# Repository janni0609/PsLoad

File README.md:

# PsLoad
 Power Supply and DC Load

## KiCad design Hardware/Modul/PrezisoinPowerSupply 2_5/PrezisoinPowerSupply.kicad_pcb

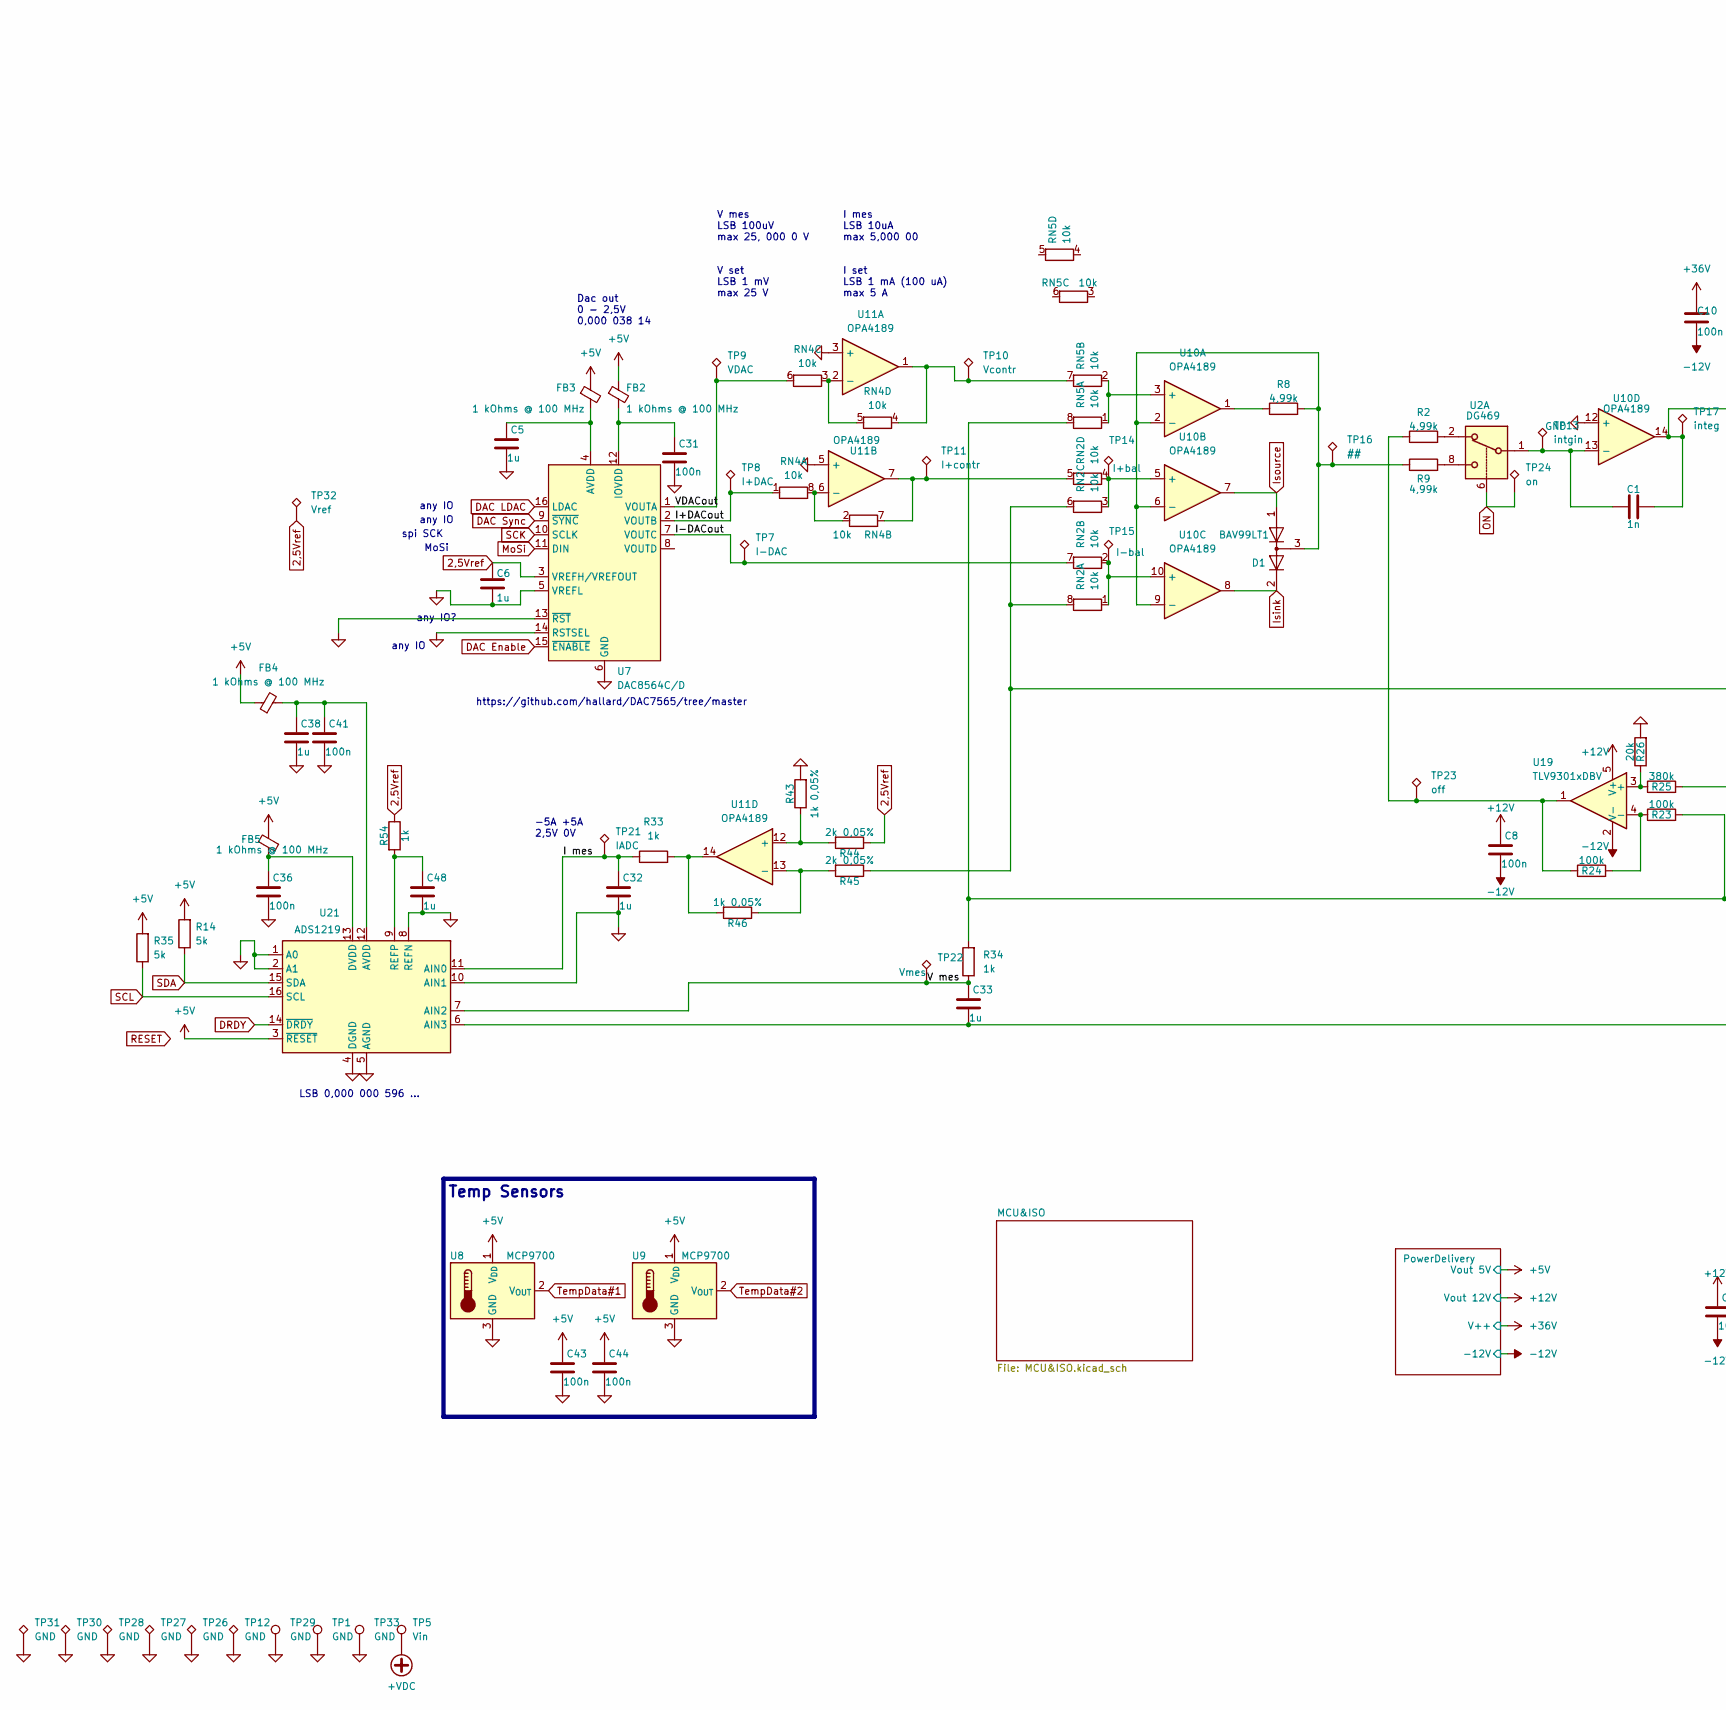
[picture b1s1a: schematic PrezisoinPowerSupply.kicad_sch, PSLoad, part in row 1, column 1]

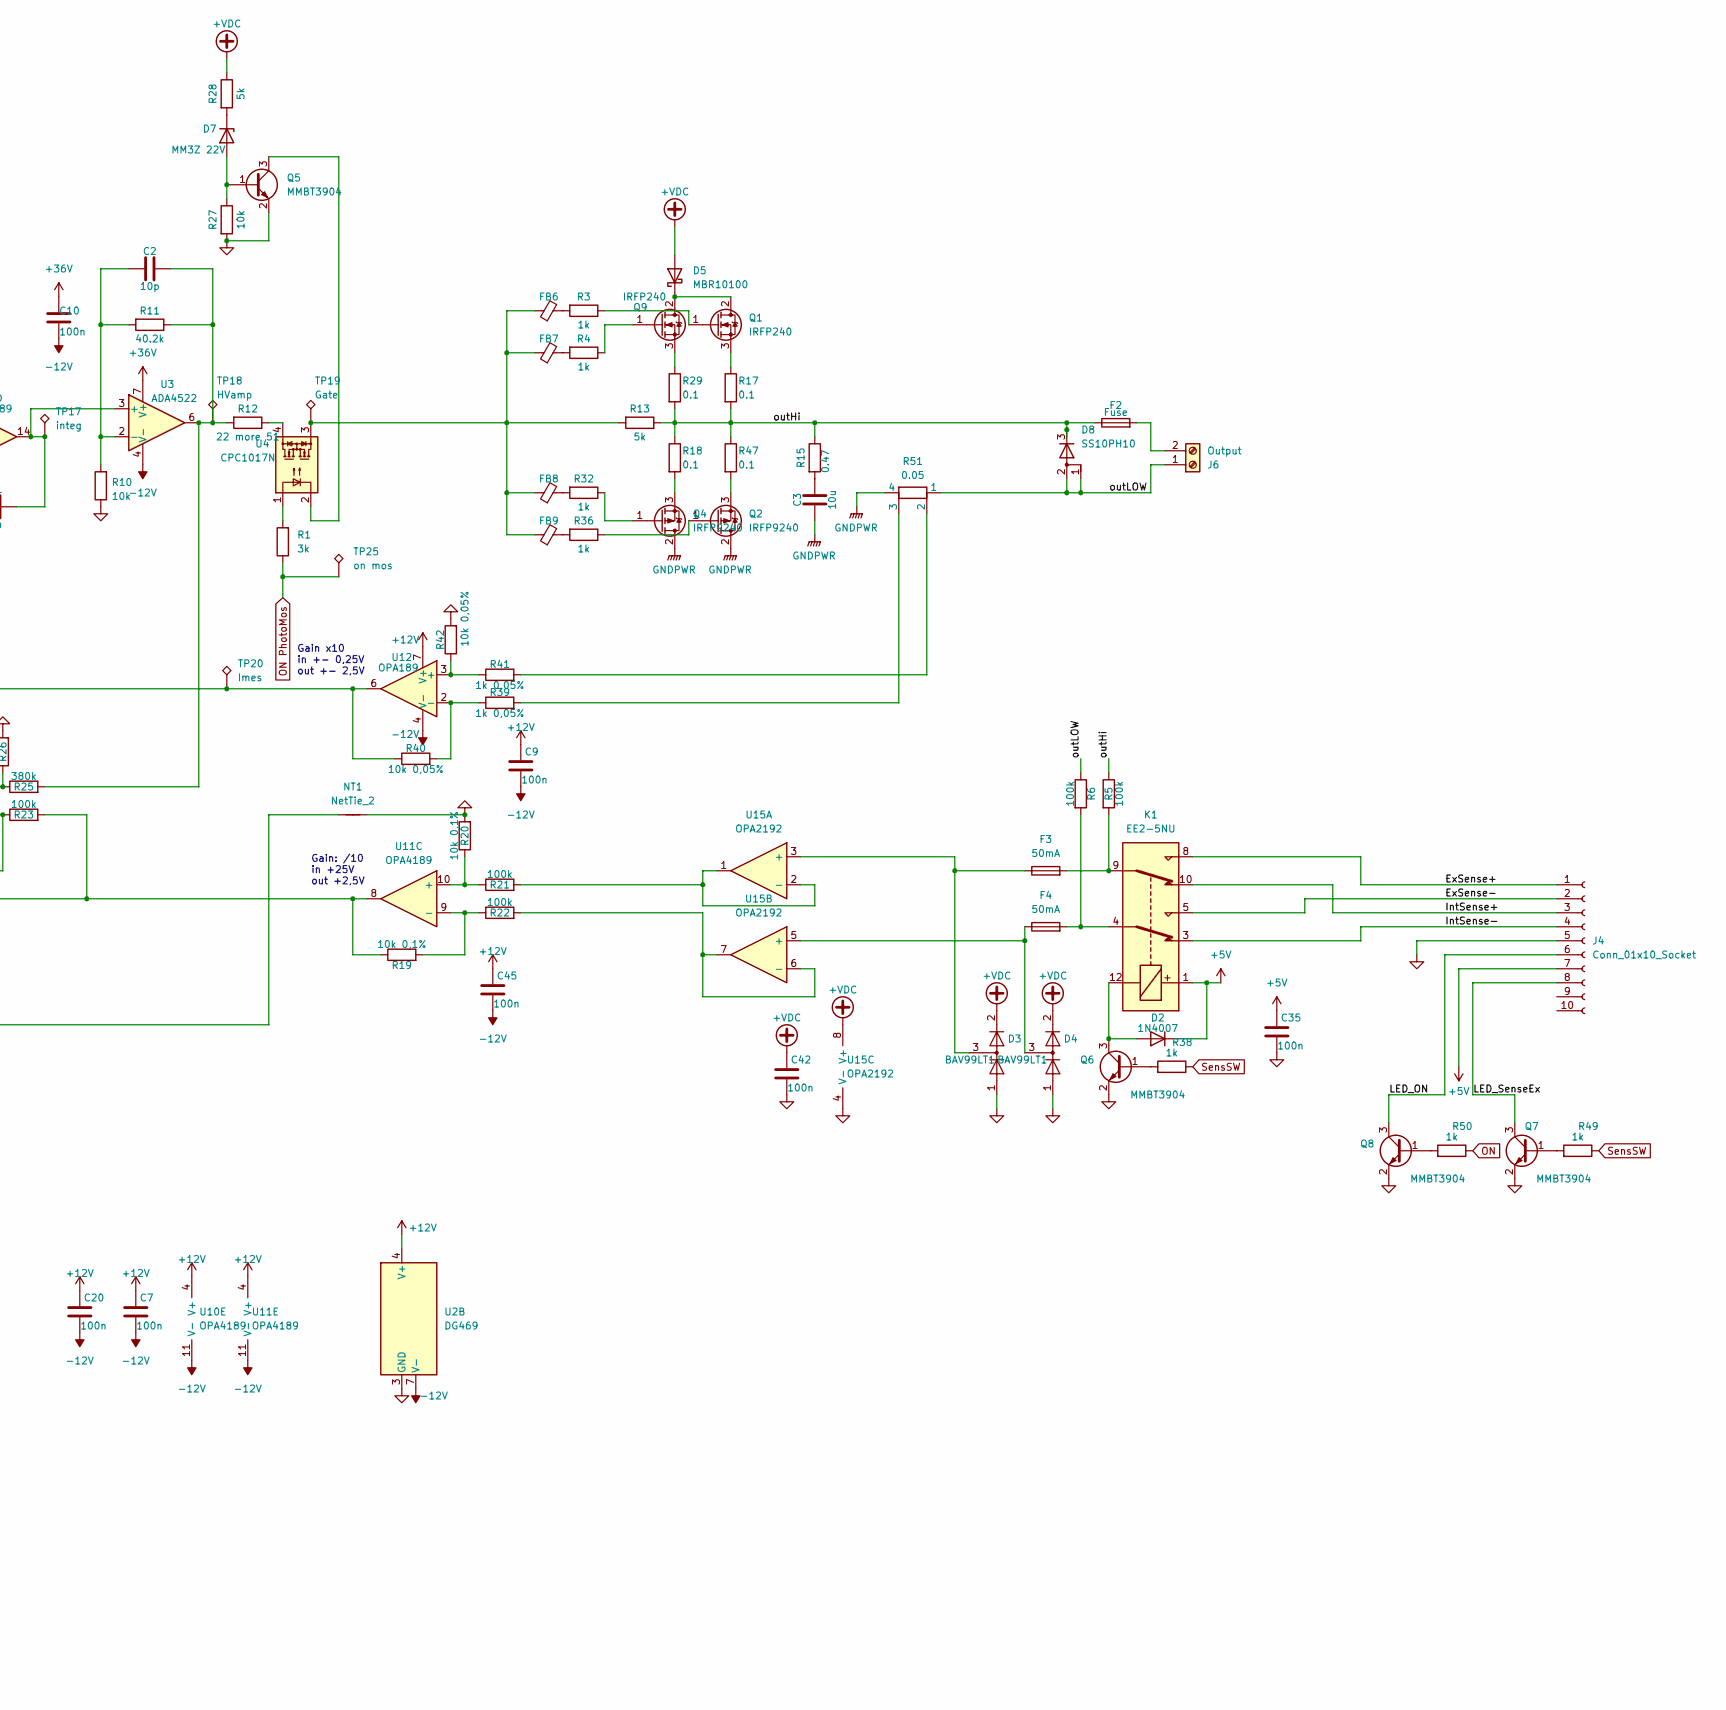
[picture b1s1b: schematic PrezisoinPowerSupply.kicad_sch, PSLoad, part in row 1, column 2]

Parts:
C1: 1n; C_0603_1608Metric
C2: 10p; C_0603_1608Metric
C3: 10u; C_1206_3216Metric
C5, C6, C32, C33, C38, C48: 1u; C_0603_1608Metric
C7, C8, C9, C10, C20, C31, C35, C36, C41, C42, C43, C44, C45: 100n; C_0603_1608Metric
D1: BAV99LT1; SOT-23
D2: 1N4007; D_SOD-123F
D3, D4: BAV99LT1; SOT-23-3
D5: MBR10100; TO-220-2_Vertical
D7: MM3Z 22V; D_SOD-323F
D8: SS10PH10; TO-277A
F2: Fuse; Fuse_Littelfuse-NANO2-451_453
F3, F4: 50mA; Fuse_0402_1005Metric
FB2, FB3, FB4, FB5, FB6, FB7, FB8, FB9: 1 kOhms @ 100 MHz; L_0603_1608Metric
J4: Conn_01x10_Socket; JST_GH_BM10B-GHS-TBT_1x10-1MP_P1.25mm_Vertical
J6: Output; AMASS_XT30PW-F_1x02_P2.50mm_Horizontal
K1: EE2-5NU; Relay_DPDT_Kemet_EE2_NU
NT1: NetTie_2; NetTie-2_SMD_Pad0.5mm
Q1, Q9: IRFP240; TO-247-3_Vertical
Q2, Q4: IRFP9240; TO-247-3_Vertical
Q5, Q6, Q7, Q8: MMBT3904; SOT-23-3
R1: 3k; R_0603_1608Metric
R2, R8, R9: 4,99k; R_0603_1608Metric
R3, R4, R32, R33, R34, R36, R38, R49, R50, R54: 1k; R_0603_1608Metric
R5, R6, R21, R22, R23, R24: 100k; R_0603_1608Metric
R10, R27: 10k; R_0603_1608Metric
R11: 40.2k; R_0603_1608Metric
R12: 22 more 51; R_0603_1608Metric
R13, R14, R28, R35: 5k; R_0603_1608Metric
R15: 0.47; R_1206_3216Metric
R17, R18, R29, R47: 0.1; R_Bare_Metal_Element_L16.3mm_W4.8mm_P15.30mm
R19, R20: 10k 0,1%; R_0603_1608Metric
R25: 380k; R_0603_1608Metric
R26: 20k; R_0603_1608Metric
R39, R41, R43, R46: 1k 0,05%; R_0603_1608Metric
R40, R42: 10k 0,05%; R_0603_1608Metric
R44, R45: 2k 0,05%; R_0603_1608Metric
R51: 0.05; R 2728 4Wire
RN2, RN4, RN5: 10k; R_Array_Convex_4x0612
TP1, TP29, TP33: GND; SMD Test Point PCWCTE
TP5: Vin; SMD Test Point PCWCTE
TP7: I-DAC; TestPoint_Pad_D1.5mm
TP8: I+DAC; TestPoint_Pad_D1.5mm
TP9: VDAC; TestPoint_Pad_D1.5mm
TP10: Vcontr; TestPoint_Pad_D1.5mm
TP11: I+contr; TestPoint_Pad_D1.5mm
TP12, TP26, TP27, TP28, TP30, TP31: GND; TestPoint_Pad_D1.5mm
TP13: intgin; TestPoint_Pad_D1.5mm
TP14: I+bal; TestPoint_Pad_D1.5mm
TP15: I-bal; TestPoint_Pad_D1.5mm
TP16: ##; TestPoint_Pad_D1.5mm
TP17: integ; TestPoint_Pad_D1.5mm
TP18: HVamp; TestPoint_Pad_D1.5mm
TP19: Gate; TestPoint_Pad_D1.5mm
TP20: Imes; TestPoint_Pad_D1.5mm
TP21: IADC; TestPoint_Pad_D1.5mm
TP22: Vmes; TestPoint_Pad_D1.5mm
TP23: off; TestPoint_Pad_D1.5mm
TP24: on; TestPoint_Pad_D1.5mm
TP25: on mos; TestPoint_Pad_D1.5mm
TP32: Vref; TestPoint_Pad_D1.5mm
U2: DG469; SOIC-8_3.9x4.9mm_P1.27mm
U3: ADA4522; SOIC-8_3.9x4.9mm_P1.27mm
U4: CPC1017N; SOP-4_3.8x4.1mm_P2.54mm
U7: DAC8564C/D; TSSOP-16_4.4x5mm_P0.65mm
U8, U9: MCP9700; TO-92_Inline
U10, U11: OPA4189; SOIC-14_3.9x8.7mm_P1.27mm
U12: OPA189; SOIC-8_3.9x4.9mm_P1.27mm
U15: OPA2192; SOIC-8_3.9x4.9mm_P1.27mm
U19: TLV9301xDBV; SOT-23-5
U21: ADS1219; TSSOP-16_4.4x5mm_P0.65mm

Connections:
2,5Vref: C6.1, R44.1, R54.1, TP32.1, U7.3 (VREFH/VREFOUT)
+5V: C35.1, C43.1, C44.1, D2.1 (K), FB2.1, FB3.1, FB4.1, FB5.2, J4.7, K1.1, R14.2, R35.2, U8.1 (V_{DD}), U9.1 (V_{DD}), U21.3 (~RESET); also elsewhere on the board
+12V: C7.1, C8.1, C9.1, C20.1, C45.1, U2.4 (V+), U10.4 (V+), U11.4 (V+), U12.7 (V+), U19.5 (V+); also elsewhere on the board
+36V: C10.1, U3.7 (V+); also elsewhere on the board
-12V: C7.2, C8.2, C9.2, C10.2, C20.2, C45.2, U2.7 (V-), U3.4 (V-), U10.11 (V-), U11.11 (V-), U12.4 (V-), U19.2 (V-); also elsewhere on the board
/ExSense+: J4.1, K1.8
/ExSense-: J4.2, K1.5
/I mes: C32.1, R33.1, TP21.1, U21.11 (AIN0)
/I+DACout: RN4.1 (R1.1), TP8.1, U7.2 (VOUTB)
/I-DACout: RN2.7 (R2.2), TP7.1, U7.7 (VOUTC)
/IntSense+: J4.3, K1.10
/IntSense-: J4.4, K1.3
/LED_ON: J4.6, Q8.3 (C)
/LED_SenseEx: J4.8, Q7.3 (C)
/V mes: C33.1, R34.1, TP22.1, U21.7 (AIN2)
/VDACout: RN4.6 (R3.2), TP9.1, U7.1 (VOUTA)
/outHi: D8.3 (K), F2.1, R5.1, R13.1, R15.1, R17.2, R18.1, R29.2, R47.1
/outLOW: D8.1 (A), D8.2 (A), J6.1, R6.1, R51.1
DAC Enable: U7.15 (~ENABLE); also elsewhere on the board
DAC LDAC: U7.16 (LDAC); also elsewhere on the board
DAC Sync: U7.9 (~SYNC); also elsewhere on the board
DRDY: U21.14 (~DRDY); also elsewhere on the board
GND: C5.2, C6.2, C31.2, C32.2, C35.2, C36.2, C38.2, C41.2, C42.2, C43.2, C44.2, C48.2, D3.1 (K), D4.1 (K), J4.5, NT1.2, Q5.2 (E), Q6.2 (E), Q7.2 (E), Q8.2 (E), R10.1, R20.2, R26.2, R27.2, R42.2, R43.2, TP1.1, TP12.1, TP26.1, TP27.1, TP28.1, TP29.1, TP30.1, TP31.1, TP33.1, U2.3 (GND), U7.5 (VREFL), U7.6 (GND), U7.13 (~RST), U7.14 (RSTSEL), U8.3 (GND), U9.3 (GND), U10.12 (+), U11.3 (+), U11.5 (+), U15.4 (V-), U21.1 (A0), U21.2 (A1), U21.4 (DGND), U21.5 (AGND), U21.8 (REFN), U21.10 (AIN1); also elsewhere on the board
GNDPWR: C3.1, Q2.2 (D), Q4.2 (D), R51.4; also elsewhere on the board
Isink: D1.2 (A), U10.8
Isource: D1.1 (K), U10.7
MoSi: U7.11 (DIN); also elsewhere on the board
unnamed: C2.2, R11.1, R12.2, R25.2, TP18.1, U3.6
unnamed: C3.2, R15.2
unnamed: D2.2 (A), K1.12, Q6.3 (C)
unnamed: D5.1 (K), Q1.2 (D), Q9.2 (D)
unnamed: D7.2 (A), Q5.1 (B), R27.1
unnamed: D7.1 (K), R28.2
unnamed: F3.2, K1.9, R5.2
unnamed: F4.2, K1.4, R6.2
unnamed: FB6.1, FB7.1, FB8.1, FB9.1, R13.2, TP19.1, U4.3
unnamed: FB6.2, R3.2
unnamed: FB7.2, R4.2
unnamed: FB8.2, R32.2
unnamed: FB9.2, R36.2
unnamed: F2.2, J6.2
unnamed: Q1.1 (G), R3.1
unnamed: Q1.3 (S), R17.1
unnamed: Q2.1 (G), R36.1
unnamed: Q2.3 (S), R47.2
unnamed: Q4.1 (G), R32.1
unnamed: Q4.3 (S), R18.2
unnamed: Q5.3 (C), U4.2
unnamed: Q6.1 (B), R38.2
unnamed: Q7.1 (B), R49.2
unnamed: Q8.1 (B), R50.2
unnamed: Q9.1 (G), R4.1
unnamed: Q9.3 (S), R29.1
unnamed: R1.2, U4.1
unnamed: R2.1, R24.1, TP23.1, U19.1
unnamed: R2.2, U2.2
unnamed: R8.1, U10.1
unnamed: R9.2, U2.8
unnamed: R12.1, U4.4
unnamed: R33.2, R46.2, U11.14
unnamed: R39.2, R51.3
unnamed: R41.2, R51.2
unnamed: RN2.1 (R1.1), RN2.2 (R2.1), TP15.1, U10.10 (+)
unnamed: R40.1, R45.1, RN2.6 (R3.2), RN2.8 (R1.2), TP20.1, U12.6
unnamed: RN2.3 (R3.1), RN2.4 (R4.1), TP14.1, U10.5 (+)
unnamed: RN2.5 (R4.2), RN4.7 (R2.2), TP11.1, U11.7
unnamed: RN4.2 (R2.1), RN4.8 (R1.2), U11.6 (-)
unnamed: RN4.3 (R3.1), RN4.5 (R4.2), U11.2 (-)
unnamed: RN4.4 (R4.1), RN5.7 (R2.2), TP10.1, U11.1
unnamed: RN5.1 (R1.1), RN5.2 (R2.1), U10.3 (+)
unnamed: R19.1, R23.2, R34.2, RN5.8 (R1.2), U11.8
unnamed: C1.2, TP17.1, U3.3 (+), U10.14
unnamed: C2.1, R10.2, R11.2, U3.2 (-)
unnamed: C5.1, FB3.2, U7.4 (AVDD)
unnamed: C31.1, FB2.2, U7.12 (IOVDD)
unnamed: D1.3 (K), R8.2, R9.1, TP16.1, U10.2 (-), U10.6 (-), U10.9 (-)
unnamed: C1.1, TP13.1, U2.1, U10.13 (-)
unnamed: R20.1, R21.1, U11.10 (+)
unnamed: R19.2, R22.1, U11.9 (-)
unnamed: R43.1, R44.2, U11.12 (+)
unnamed: R45.2, R46.1, U11.13 (-)
unnamed: R41.1, R42.1, U12.3 (+)
unnamed: R39.1, R40.2, U12.2 (-)
unnamed: D3.3 (K), F3.1, U15.3 (+)
unnamed: R21.2, U15.1, U15.2 (-)
unnamed: D4.3 (K), F4.1, U15.5 (+)
unnamed: R22.2, U15.6 (-), U15.7
unnamed: R25.1, R26.1, U19.3 (+)
unnamed: R23.1, R24.2, U19.4 (-)
unnamed: C33.2, NT1.1, U21.6 (AIN3)
unnamed: C38.1, C41.1, FB4.2, U21.12 (AVDD)
unnamed: C36.1, FB5.1, U21.13 (DVDD)
unnamed: C48.1, R54.2, U21.9 (REFP)
ON: R50.1, TP24.1, U2.6; also elsewhere on the board
ON PhotoMos: R1.1, TP25.1; also elsewhere on the board
SCK: U7.10 (SCLK); also elsewhere on the board
SCL: R35.1, U21.16 (SCL); also elsewhere on the board
SDA: R14.1, U21.15 (SDA); also elsewhere on the board
SensSW: R38.1, R49.1; also elsewhere on the board
TempData#1: U8.2 (V_{OUT}); also elsewhere on the board
TempData#2: U9.2 (V_{OUT}); also elsewhere on the board

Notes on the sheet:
https://github.com/hallard/DAC7565/tree/master
any IO
Temp Sensors
Dac out 0 - 2,5V 0,000 038 14
LSB 0,000 000 596 ...
spi SCK
any IO?
Gain: /10 in +25V out +2,5V
MoSi
-5A +5A 2,5V 0V
V mes LSB 100uV max 25, 000 0 V
V set LSB 1 mV max 25 V
Gain x10 in +- 0,25V out +- 2,5V
I mes LSB 10uA max 5,000 00
I set LSB 1 mA (100 uA) max 5 A

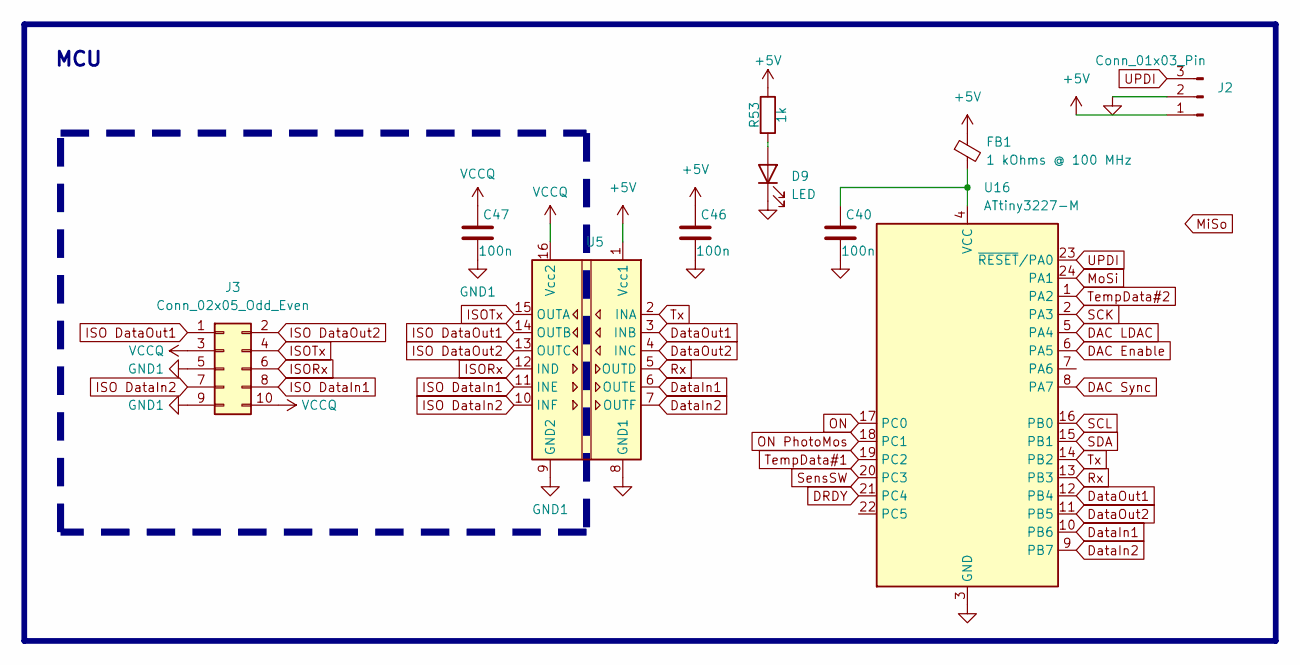
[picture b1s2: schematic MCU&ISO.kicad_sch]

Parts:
C40, C46, C47: 100n; C_0603_1608Metric
D9: LED; LED_0603_1608Metric
FB1: 1 kOhms @ 100 MHz; L_0603_1608Metric
J2: Conn_01x03_Pin; PinSocket_1x03_P2.54mm_Vertical
J3: Conn_02x05_Odd_Even; IDC-Header_2x05_P2.54mm_Vertical
R53: 1k; R_0603_1608Metric
U5: ISO7763FDBQ; SSOP-16_3.9x4.9mm_P0.635mm
U16: ATtiny3227-M; QFN-24-1EP_4x4mm_P0.5mm_EP2.6x2.6mm

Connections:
+5V: C46.1, FB1.1, J2.1, R53.1, U5.1 (Vcc1); also elsewhere on the board
DAC Enable: U16.6 (PA5); also elsewhere on the board
DAC LDAC: U16.5 (PA4); also elsewhere on the board
DAC Sync: U16.8 (PA7); also elsewhere on the board
DRDY: U16.21 (PC4); also elsewhere on the board
DataIn1: U5.6 (OUTE), U16.10 (PB6)
DataIn2: U5.7 (OUTF), U16.9 (PB7)
DataOut1: U5.3 (INB), U16.12 (PB4)
DataOut2: U5.4 (INC), U16.11 (PB5)
GND: C40.2, C46.2, D9.1 (K), J2.2, U5.8 (GND1), U16.3 (GND), U16.25 (GND); also elsewhere on the board
GND1: C47.2, J3.5, J3.9, U5.9 (GND2)
ISO DataIn1: J3.8, U5.11 (INE)
ISO DataIn2: J3.7, U5.10 (INF)
ISO DataOut1: J3.1, U5.14 (OUTB)
ISO DataOut2: J3.2, U5.13 (OUTC)
ISORx: J3.6, U5.12 (IND)
ISOTx: J3.4, U5.15 (OUTA)
MoSi: U16.24 (PA1); also elsewhere on the board
unnamed: D9.2 (A), R53.2
unnamed: C40.1, FB1.2, U16.4 (VCC)
ON: U16.17 (PC0); also elsewhere on the board
ON PhotoMos: U16.18 (PC1); also elsewhere on the board
Rx: U5.5 (OUTD), U16.13 (PB3)
SCK: U16.2 (PA3); also elsewhere on the board
SCL: U16.16 (PB0); also elsewhere on the board
SDA: U16.15 (PB1); also elsewhere on the board
SensSW: U16.20 (PC3); also elsewhere on the board
TempData#1: U16.19 (PC2); also elsewhere on the board
TempData#2: U16.1 (PA2); also elsewhere on the board
Tx: U5.2 (INA), U16.14 (PB2)
UPDI: J2.3, U16.23 (~RESET/PA0)
VCCQ: C47.1, J3.3, J3.10, U5.16 (Vcc2)

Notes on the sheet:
MCU

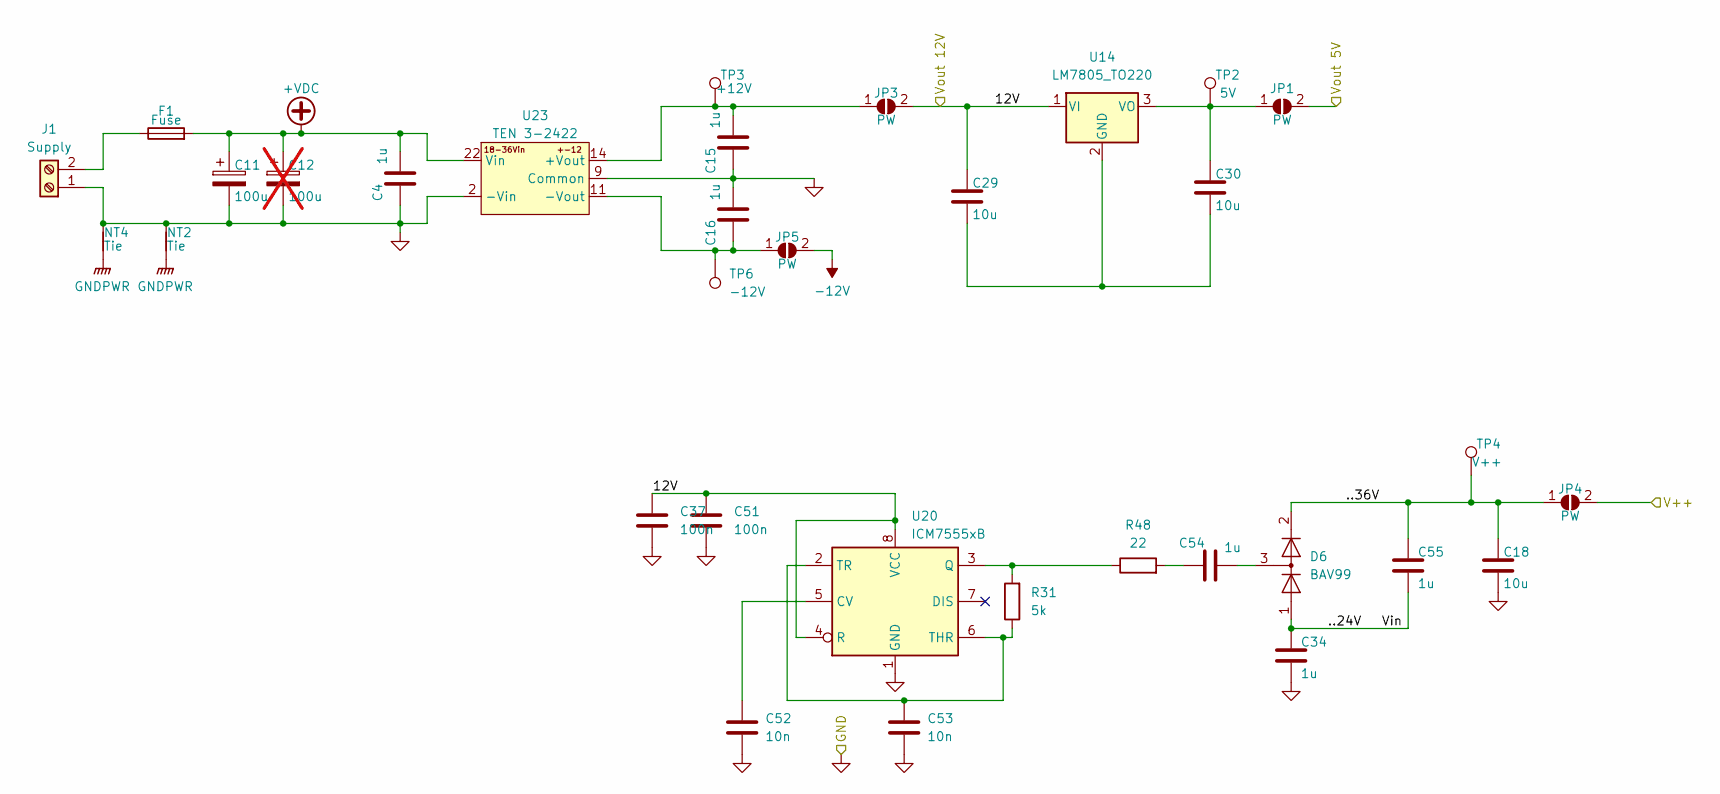
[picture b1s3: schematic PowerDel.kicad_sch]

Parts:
C4, C15, C16, C34, C54, C55: 1u; C_1206_3216Metric
C11: 100u; CP_Elec_8x10.5
C12: 100u; CP_Elec_8x10.5; not fitted
C18, C29, C30: 10u; C_1206_3216Metric
C37, C51: 100n; C_0603_1608Metric
C52, C53: 10n; C_0603_1608Metric
D6: BAV99; SOT-23-3
F1: Fuse; Fuse_Littelfuse-NANO2-451_453
J1: Supply; AMASS_XT30PW-M_1x02_P2.50mm_Horizontal
JP1, JP3, JP4, JP5: PW; SolderJumper-2_P1.3mm_Open_RoundedPad1.0x1.5mm
NT2, NT4: Tie; NetTie-2_SMD_Pad2.0mm
R31: 5k; R_0603_1608Metric
R48: 22; R_0603_1608Metric
TP2: 5V; SMD Test Point PCWCTE
TP3: +12V; SMD Test Point PCWCTE
TP4: V++; SMD Test Point PCWCTE
TP6: -12V; SMD Test Point PCWCTE
U14: LM7805_TO220; TO-220-3_Vertical
U20: ICM7555xB; SOIC-8_3.9x4.9mm_P1.27mm
U23: TEN 3-2422; Traco TEN 3-2422

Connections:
+5V: JP1.2 (B); also elsewhere on the board
+12V: C29.1, C37.1, C51.1, JP3.2 (B), U14.1 (VI), U20.4 (R), U20.8 (VCC); also elsewhere on the board
+36V: JP4.2 (B); also elsewhere on the board
-12V: JP5.2 (B); also elsewhere on the board
/PowerDelivery/..36V: C18.1, C55.1, D6.2 (A), JP4.1 (A), TP4.1
GND: C4.1, C11.2, C12.2, C15.1, C16.2, C18.2, C34.2, C37.2, C51.2, C52.2, C53.2, J1.1, NT2.2, NT4.2, U20.1 (GND), U23.2 (-Vin), U23.3 (-Vin), U23.9 (Common), U23.16 (Common); also elsewhere on the board
GNDPWR: NT2.1, NT4.1; also elsewhere on the board
unnamed: C54.1, R48.2
unnamed: C54.2, D6.3 (K)
unnamed: F1.1, J1.2
unnamed: C30.1, JP1.1 (A), TP2.1, U14.3 (VO)
unnamed: C15.2, JP3.1 (A), TP3.1, U23.14 (+Vout)
unnamed: C16.1, JP5.1 (A), TP6.1, U23.11 (-Vout)
unnamed: C29.2, C30.2, U14.2 (GND)
unnamed: C52.1, U20.5 (CV)
unnamed: R31.2, R48.1, U20.3 (Q)
unnamed: C53.1, R31.1, U20.2 (TR), U20.6 (THR)

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
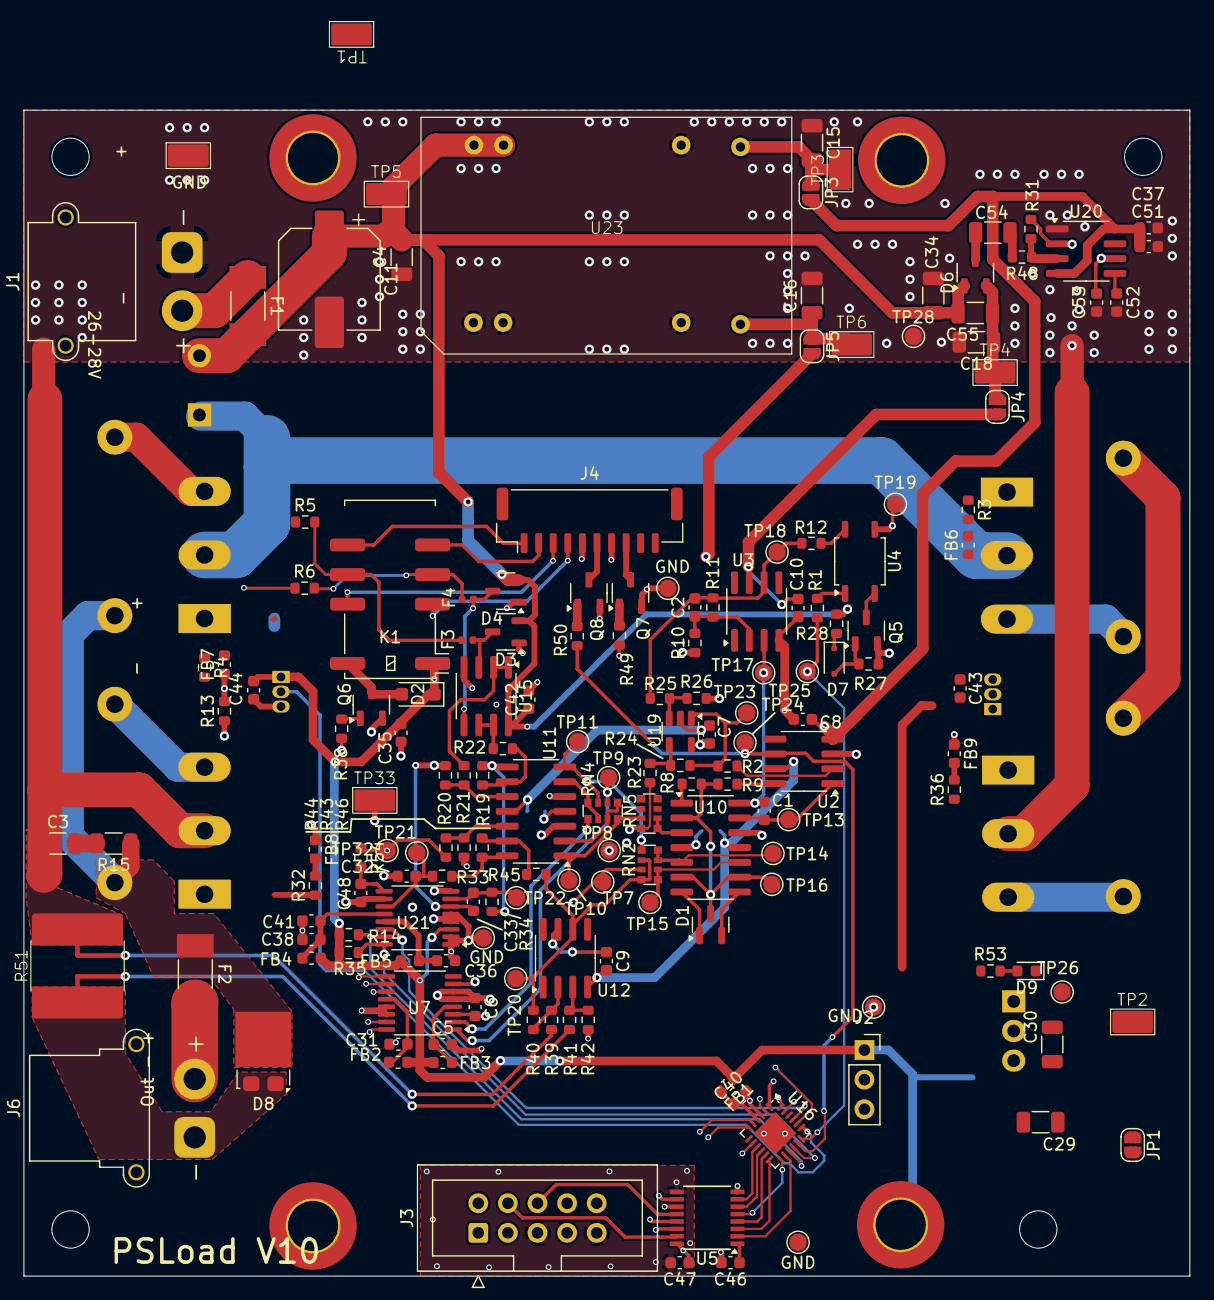
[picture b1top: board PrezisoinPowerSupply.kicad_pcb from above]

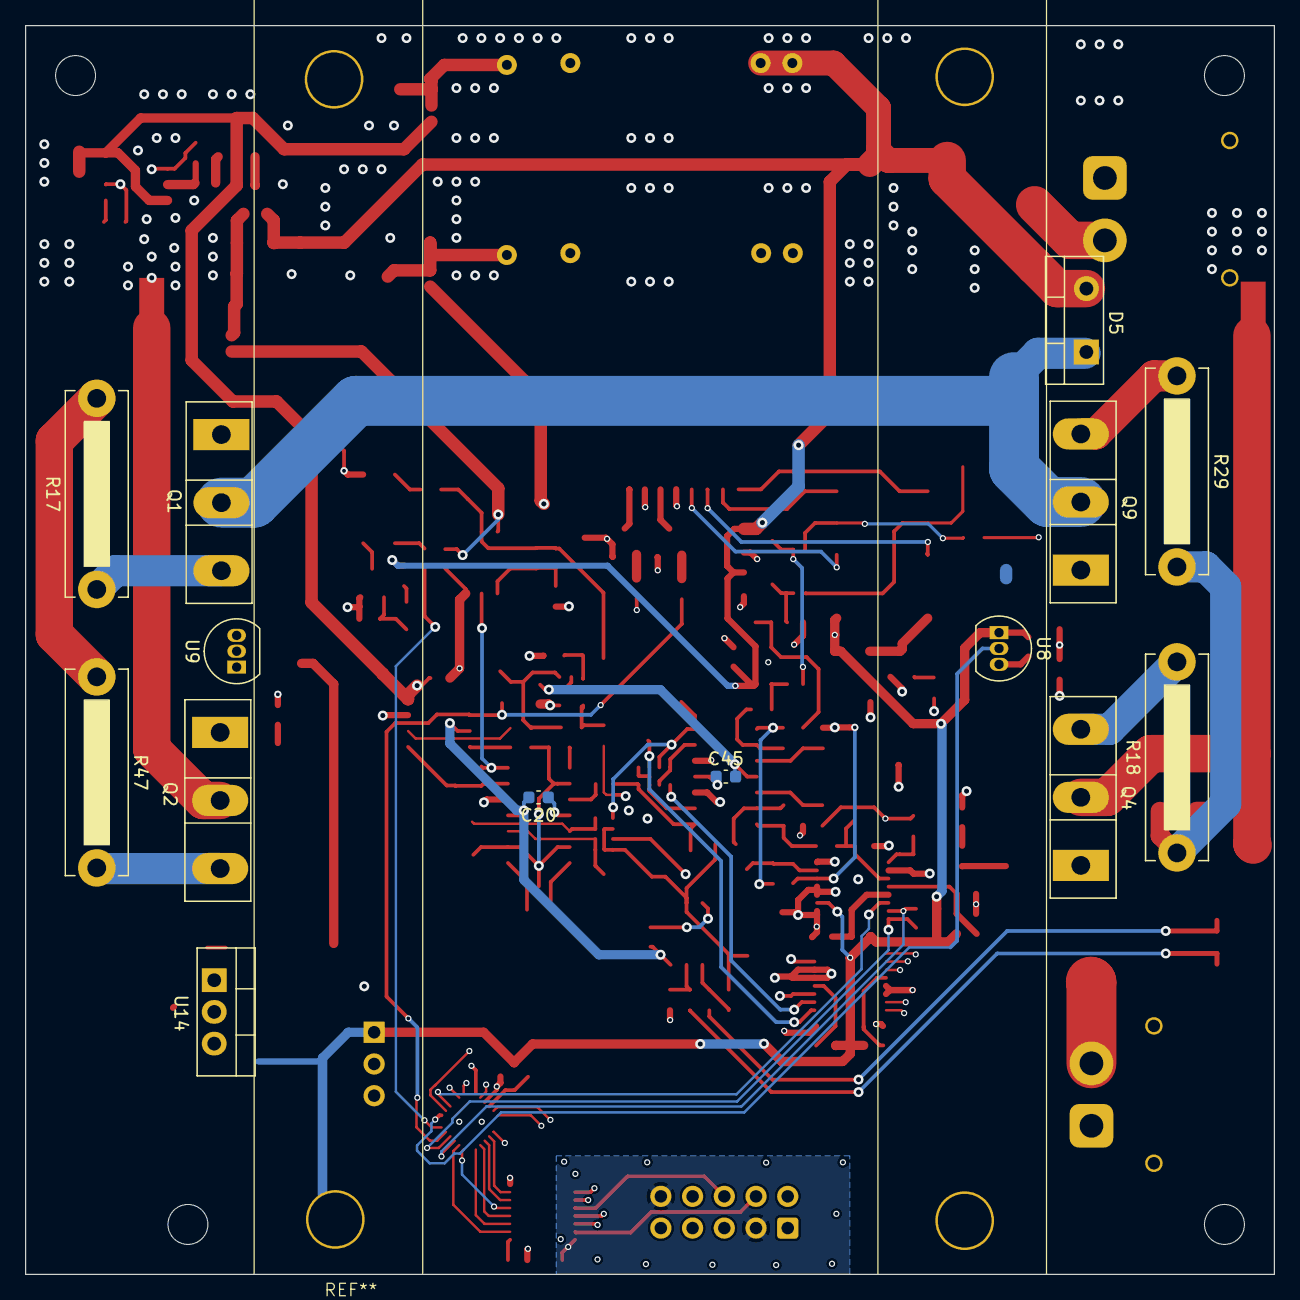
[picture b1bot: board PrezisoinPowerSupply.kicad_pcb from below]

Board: 4 copper layers, 100.0 x 100.0 mm, 184 parts (14 on the bottom side), 130 nets.

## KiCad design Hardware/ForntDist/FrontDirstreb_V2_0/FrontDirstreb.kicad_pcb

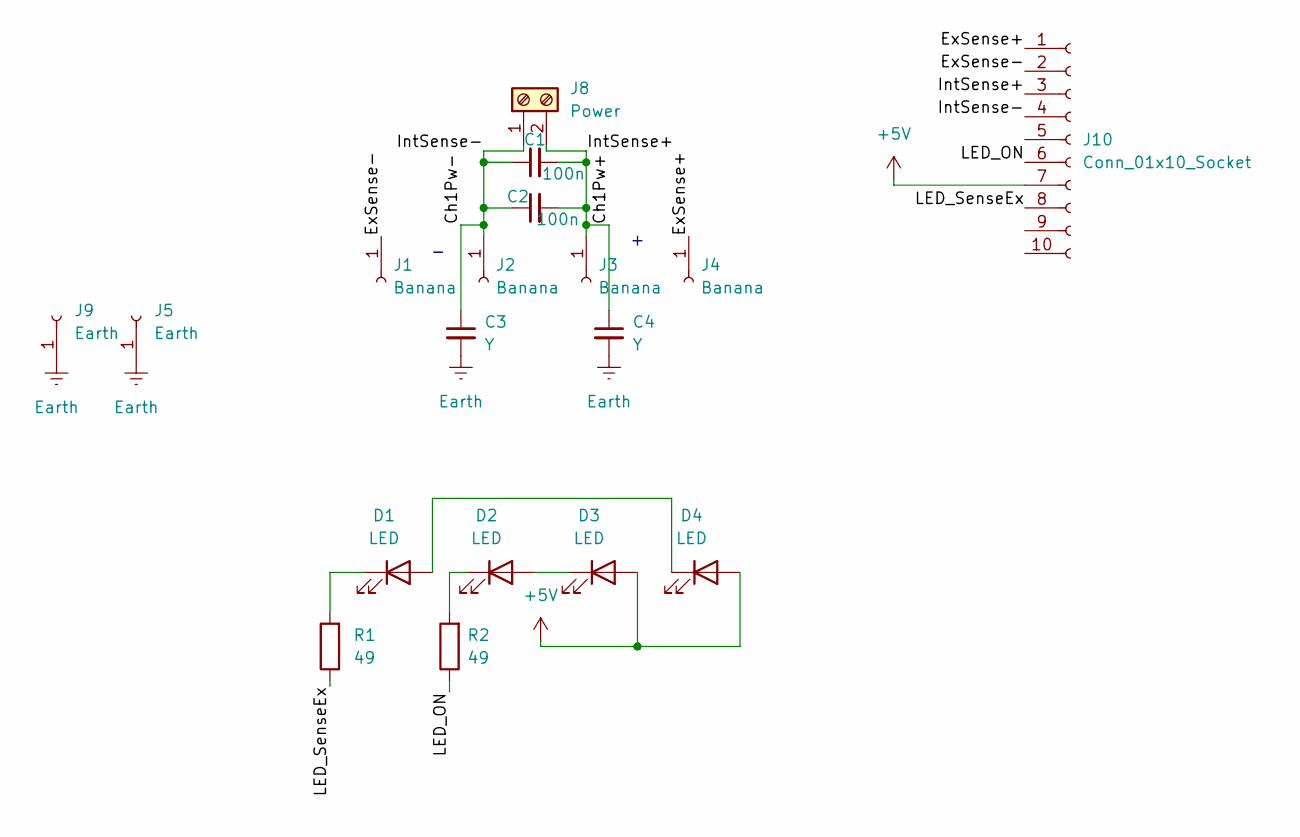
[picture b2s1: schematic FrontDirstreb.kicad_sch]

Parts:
C1, C2: 100n; C_1206_3216Metric
C3, C4: Y; C_Rect_L13.0mm_W4.0mm_P10.00mm_FKS3_FKP3_MKS4
D1, D2, D3, D4: LED; LED_D3.0mm_FlatTop
J1, J2, J3, J4: Banana; BananaSocket
J5, J9: Earth; SolderWire-1.5sqmm_1x01_D1.7mm_OD3.9mm
J8: Power; AMASS_XT30PW-M_1x02_P2.50mm_Horizontal
J10: Conn_01x10_Socket; JST_GH_BM10B-GHS-TBT_1x10-1MP_P1.25mm_Vertical
R1, R2: 49; R_0603_1608Metric

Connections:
+5V: D3.2 (A), D4.2 (A), J10.7
/Ch1Pw+: C1.2, C2.2, C4.1, J3.1, J8.2, J10.3
/Ch1Pw-: C1.1, C2.1, C3.1, J2.1, J8.1, J10.4
/ExSense+: J4.1, J10.1
/ExSense-: J1.1, J10.2
/LED_ON: J10.6, R2.1
/LED_SenseEx: J10.8, R1.1
Earth: C3.2, C4.2, J5.1, J9.1
unnamed: D1.2 (A), D4.1 (K)
unnamed: D1.1 (K), R1.2
unnamed: D2.2 (A), D3.1 (K)
unnamed: D2.1 (K), R2.2

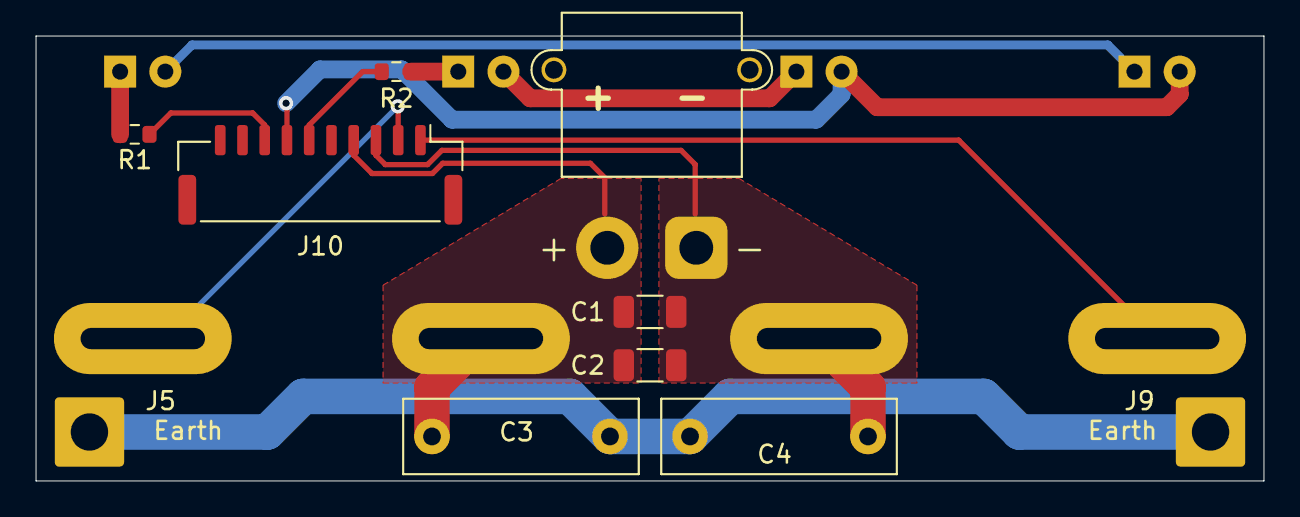
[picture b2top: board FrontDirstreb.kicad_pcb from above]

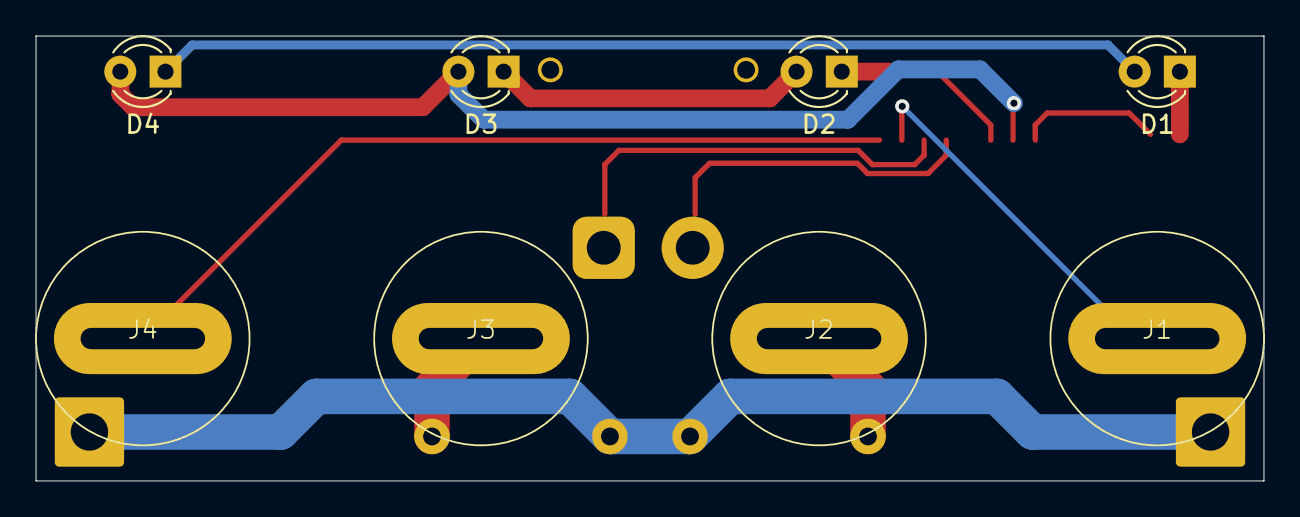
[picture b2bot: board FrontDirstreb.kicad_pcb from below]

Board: 2 copper layers, 69.0 x 25.0 mm, 18 parts (8 on the bottom side), 12 nets.

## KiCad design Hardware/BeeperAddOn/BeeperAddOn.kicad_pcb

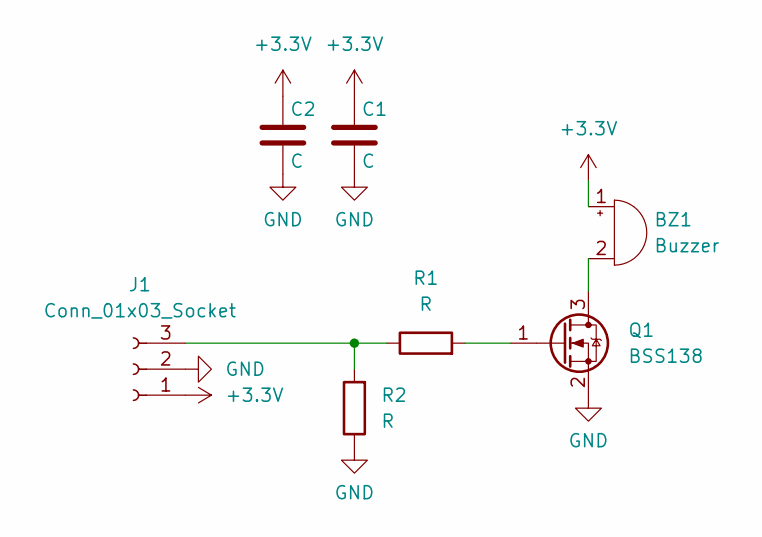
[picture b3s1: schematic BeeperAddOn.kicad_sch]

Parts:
BZ1: Buzzer; Buzzer_12x9.5RM7.6
C1, C2: C; C_0603_1608Metric
J1: Conn_01x03_Socket; PinSocket_1x03_P2.54mm_Vertical
Q1: BSS138; SOT-23-3
R1, R2: R; R_0603_1608Metric

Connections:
+3.3V: BZ1.1 (+), C1.1, C2.1, J1.1
GND: C1.2, C2.2, J1.2, Q1.2 (S), R2.1
unnamed: BZ1.2 (-), Q1.3 (D)
unnamed: J1.3, R1.1, R2.2
unnamed: Q1.1 (G), R1.2

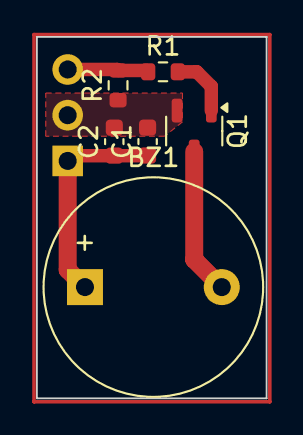
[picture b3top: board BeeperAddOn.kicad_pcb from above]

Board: 2 copper layers, 12.8 x 20.1 mm, 7 parts (1 on the bottom side), 5 nets.
